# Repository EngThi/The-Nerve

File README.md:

# The Nerve Automation Motherboard

> [!IMPORTANT]
> Reviewer, this project is a custom board placed in Tier 3. To stay within the $100 budget including international shipping fees and taxes, Version A (Round TFT) is the primary build configuration. All components are hand-soldered.

The Nerve is a modular controller for automation workflows and video pipelines. It uses an ESP32-S3 for native Wi-Fi, Bluetooth, and USB HID support.

[Specs](#hardware) | [Logs](JOURNAL.md) | [Budget](BLUEPRINT_BUDGET.md) | [Production](hardware/production/)

---

## Hardware Design

The PCB was designed in EasyEDA and the enclosure in OnShape.

### Enclosure Design

- [OnShape Public Link](https://cad.onshape.com/documents/f5fe8f1a3f0d54ab7cd3f1d7/w/a16133ebbda184e0e50a9073/e/bf72140826f3054b8f947155?renderMode=0&uiState=6a2071693fc56d9f8f5e1dc7)
- [Tinkercad 3D Model](https://www.tinkercad.com/things/edG28wTrG8o-enclousure-the-nerve?sharecode=HdeJpYusIbuaaVPp3prye_n_lixCraDDIvdvkDYTo2M)

### PCB Layout

- [Project Link in the Editor](https://pro.easyeda.com/editor#id=794fe6f5b1b64e09b8597b022e057335)

### BOM (Version A - Round TFT)
| Part | Description | Price | Link |
| :--- | :--- | :--- | :--- |
| **ESP32-S3-DevKit-LiPo** | Native USB HID and built-in LiPo charging. | $8.70 | [Olimex](https://www.olimex.com/Products/IoT/ESP32-S3/ESP32-S3-DevKit-Lipo.html) |
| **Custom PCB (5pcs)** | 2-layer PCB fabrication. | $4.00 | JLCPCB |
| **Toggle Switch Missile Cover** | Safety arming switch | $3.73 | [AliExpress](https://aliexpress.com/item/1005006733525021.html) |
| **Outemu MX Switches (5pcs)** | Mechanical switches | $2.12 | [Shopee](https://shopee.com.br/Switch-Outemu-Para-Teclado-Mec%C3%A2nico-Diversas-Cores-Blue-Red-Brown-Green-Purple-Frete-Gr%C3%A1tis-i.374734112.23418702594?xptdk=89085a82-ef5b-4cdc-b985-b933109bc5e0) |
| **K-Silver JH16 Hall Joystick (2x)**| Hall Effect analog stick | $8.12 | [AliExpress](https://aliexpress.com/item/1005008728261473.html) |
| **EC11 Rotary Encoder (10pcs)** | Rotary input | $2.58 | [AliExpress](https://aliexpress.com/item/2001241262.html) |
| **JST-PH 2.0mm 2P Connector** | Required for battery connection | $1.31 | [AliExpress](https://aliexpress.com/item/33024777806.html) |
| **Round TFT GC9A01 Display** | 1.28 inch SPI display. | $1.38 | [AliExpress](https://aliexpress.com/item/1005008284550510.html) |
| **LiPo 1800mAh 3.7V Battery** | Standalone power source. | $5.05 | [Shopee](https://shopee.com.br/Bateria-Lipo-1800mah-3.7v-3-Fios-10x34x50-3-7v-Lithium-1s1p-i.389386479.55550251664?xptdk=ee7023c0-3a92-42a8-9799-b4aa47fd9676) |
| **SMD Components Batch** | LCSC Caps, Resistors, ICs (LS7183N-S) | $14.38 | LCSC |

*(Full details and shipping/taxes breakdown in the [Hardware Budget](BLUEPRINT_BUDGET.md) and [BOM CSV](the_nerve_bom.csv))*

---

## How to Use

So, The Nerve works like a node or a kind of independent trigger that communicates with your computer (or server, those types of HID interfaces, etc) to run automated tasks. I like the part of triggering n8n/general webhooks or running FFmpeg video processing scripts, controlling something on your PC

### Hardware Setup and Firmware Flashing
1. **Wire the Panel:** Connect the Joystick to the `ADC1` pins (Pins 1 and 2), the Rotary Encoder to the Quadrature Decoder pins (Pins 15 and 16) and the Cherry MX Switch and the Missile Toggle to their respective JST ports, according to the [Wiring Diagram](assets/diagrams/EXTERNAL_WIRING_GUIDE.png) that is right below. This way you can swap ports but they have to be compatible with the type of signal and mechanics of that device you are going to use.

2. **Flash the Firmware:** Connect the ESP32 via USB-C. Install MicroPython on the board and upload the `firmware/main.py` file (or whatever you develop for your own type of use). You can improve or change this entirely, since I developed it to be multi-use and very customizable. Use different types of components, parts, etc

3. **Turn on:** You can turn it on through the USB-C cable or totally independently using the 1800mAh LiPo battery (the ProS3 and even the new one from Olimex has built-in charging) . Upon turning on, it plays a startup tone and the RGB LED turns blue.

### Operation
- **Safety Switch (Safety Lock):** Before running any command, you must lift the switch cover and turn it on. The system will be armed and an LED indicator will light up.
- **Intensity Selector (Rotary Encoder):** Turn the encoder to adjust the "Intensity Level" (0 to 100). The RGB LED changes from blue to red to visually represent the intensity level you are setting for your automation task.

- **Timeline Navigation (Joystick):** Move the joystick to adjust the X/Y parameters (useful for navigating the timeline or adjusting the visual positioning in your scripts).
- **Execute (Cherry MX Switch):** Press the mechanical switch to fire the command. If the missile switch is *armed*, it will flash white, play an execution tone and send a JSON payload via serial (or via Wi-Fi through webhooks) containing all the dial and joystick parameters. If it's *disarmed*, it will flash red and play an error warning tone.

 Open n8n and import the workflows found in the `automation/n8n/flows/` directory.

The `trigger_executor.json` file brings a script that waits for a webhook.

A local Python script on your PC (or directly on the ESP32 via Wi-Fi) listens to the JSON serial output from The Nerve and forwards it to your n8n webhook (or wherever it is, kinda), which then parses the "Hype Level" and Joystick parameters to run the logic of the `video_pipeline.json` file.

I think that's pretty much it :P

---

---

## Build and Budget

The total delivered cost for Version A is **$99.77**.

Detailed evidence can be found in the [Hardware Budget](BLUEPRINT_BUDGET.md).

### Evidence Gallery

---

_Designed by ChefThi for Hack Club Blueprint._

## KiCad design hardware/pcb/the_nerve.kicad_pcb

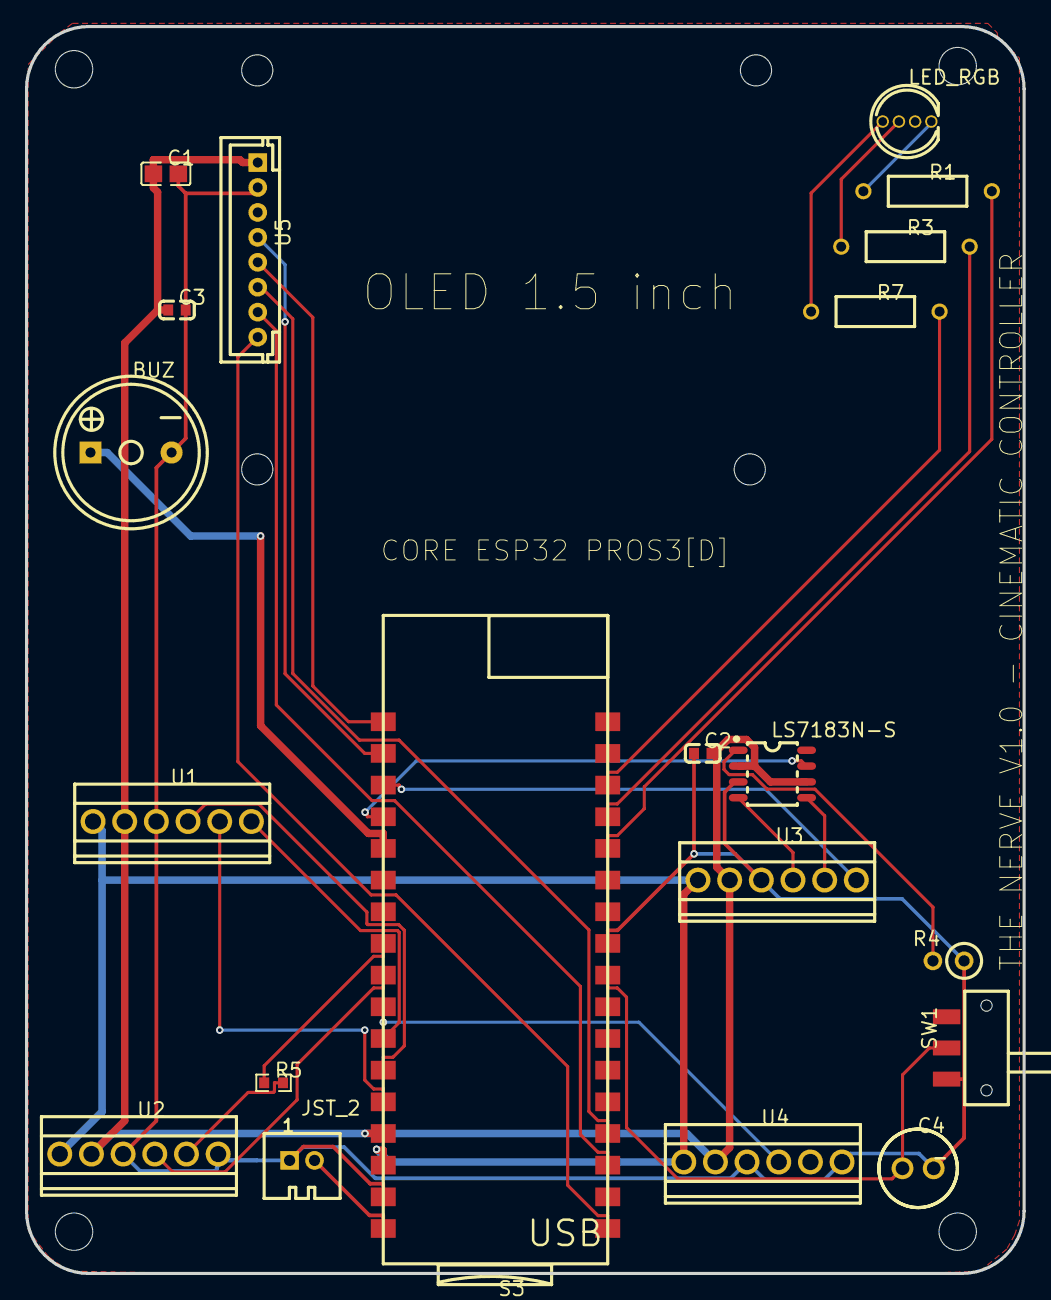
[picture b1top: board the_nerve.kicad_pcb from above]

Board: 2 copper layers, 80.0 x 100.0 mm, 20 parts (0 on the bottom side), 29 nets.

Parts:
BUZ: PASSIVE BUZZER
C1: C0805
C2, C3: 100nF; C0603
C4: 100uF; CAP-TH_BD6.3-P2.5-D0.6-FD-RYHG35V100UF
JST_2: 2.0-2P ZZDK; HDR-TH_2P-P2.00-V-F-2
LED_RGB: LED-RGB 共阴 插件 直径5MM; LED-TH_4P-BD5.8-P1.30
LS7183N-S: LS7183N-S; SOIC-8_L4.9-W3.9-P1.27-LS6.0-TL
R1, R3, R7: 220Ω; RES-TH_BD2.4-L6.3-P10.30-D0.6
R4: 2kΩ; RESISTOR-VERTICAL 1/4W 2.5MM
R5: R0603
S3: ESP32 ProS3; PROS3-SMD
SW1: MST-12D18G4 SPDT SLIDE SWITCH; SW-SMD_MST-12D18G4-SPDT-SLIDE-SWITCH
U1, U2, U3, U4: CONN-TH_6P-P2.54_KF128-2.54-6P
U5: CONN-TH_8P-P2.00_HCTL_PH-8A_C2908629

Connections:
3V3: C1.1, C2.2, C3.1, LS7183N-S.2, LS7183N-S.6, S3.4, U1.2, U2.2, U3.2, U4.2, U5.1
BUZZER: BUZ.1, S3.13
DOWN: LS7183N-S.7, S3.14
ENC_A: LS7183N-S.4, U3.4
ENC_B: LS7183N-S.5, U3.5
ENC_SW: S3.15, U3.6
GND_L: BUZ.2, C1.2, C2.1, C3.2, C4.2, JST_2.1, LS7183N-S.3, R4.1, S3.2, S3.25, SW1.1, U1.3, U2.3, U2.6, U3.3, U4.3, U4.6, U5.2
IO4: S3.8, U4.4
IO5: S3.9, U2.4
IO21: R5.2, U2.5
JOY_SW: S3.7, U1.6
JOY_X: S3.5, U1.5
JOY_Y: S3.6, U1.4
LED_BLUE: R7.2, S3.20
LED_GREEN: R3.2, S3.21
LED_RED: R1.2, S3.22
LED_RGB_1: LED_RGB.1, R1.1
LED_RGB_3: LED_RGB.3, R3.1
LED_RGB_4: LED_RGB.4, R7.1
LS7183N-S_1: LS7183N-S.1, R4.2
OLED_CS: S3.31, U5.6
OLED_DC: S3.32, U5.7
OLED_MOSI: S3.16, U5.4
OLED_RES: S3.34, U5.8
OLED_SCK: S3.17, U5.5
RST: C4.1, S3.26, SW1.2
S3_5V: S3.3, U1.1, U2.1, U3.1, U4.1
S3_10: R5.1, S3.10
VBAT: JST_2.2, S3.1

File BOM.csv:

ID,Name,Designator,Quantity,Manufacturer,Supplier,Supplier Part,Price,Link,Notes
1,C0805 10uF,C1,1,Samsung,LCSC,C96445,Decoupling Cap
2,Resistor 220Ω,R1/R3/R7,3,Tyohm,LCSC,C410657,0.01,https://jlcpcb.com/partdetail/TyoHM-RN_1_4W_220R_F_T_BA1/C410657,Current Limiting
3,Resistor 330Ω,R5,1,YAGEO,LCSC,C105881,0.0084,https://lcsc.com/product-detail/Chip-Resistor-Surface-Mount_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,LED Resistor
4,Resistor 2kΩ,R4,1,UNI-ROYAL,LCSC,C58680,0.008,https://www.lcsc.com/product-detail/C58680.html,Pull-up
5,Conn 6-Pin 2.54mm,U1-U4,4,KEFA,LCSC,C474924,0.637,https://lcsc.com/product-detail/Pluggable-System-Terminal-Bl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,Screw Terminals
6,Conn JST 2-Pin,JST_2,1,SHOU HAN,LCSC,C18185603,0.014,https://lcsc.com/product-detail/Wire-To-Board-Wire-To-Wire-C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,Battery Conn (2.0mm pitch)
7,Conn 8-Pin 2.00mm,U4_Ext,1,HCTL,LCSC,C2908629,0.044,https://lcsc.com/product-detail/Wire-To-Board-Wire-To-Wire-C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,Expansion Header
8,Passive Buzzer,BUZ,1,Generic,LCSC,C9900008742,0.0002,Audio Feedback
9,Cap 100nF,C2/C3,2,AIDE,LCSC,C49326605,0.0017,https://lcsc.com/product-detail/Multilayer-Ceramic-Capacitor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,Filter Cap
10,Cap 100uF,C4,1,HONOR,LCSC,C48970442,0.012,https://lcsc.com/product-detail/Aluminum-Electrolytic-Capaci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,Bulk Cap
11,LED RGB 5mm,LED_RGB,1,Generic,LCSC,C9900015469,0.0057,https://lcsc.com/product-detail/Light-Emitting-Diodes-LED_C9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,Status LED
12,IC Decoder LS7183N-S,U_DEC,1,LSI/CSI,LCSC,C3234982,6.32,https://lcsc.com/product-detail/Encoders_LSI-CSI-LS7183N-S_C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,Quadrature Decoder
13,Slide Switch SPDT,SW1,1,SHOU HAN,LCSC,C49023767,0.08,https://lcsc.com/product-detail/Slide-Switches_SHOU-HAN-MST-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,Power Switch
14,Battery LiPo 3000mAh,BATT_OPT1,1,Hiteuoms,Amazon,B0DP2JKFJG,9.99,https://www.amazon.com/dp/B0DP2JKFJG,"Power Source (Option 1, 3000mAh, JST 1.25mm - REQUIRES ADAPTER)"
15,Battery LiPo 2200mAh,BATT_OPT2,1,OXWINOU,Amazon,B0CTQ6VBB6,9.98,https://www.amazon.com/dp/B0CTQ6VBB6,"Power Source (Option 2, 2200mAh, JST 2.0mm - Direct Fit)"
16,Switch Cherry MX Blue,SW_MECH,1,Cherry,MechKeyboards,MX2A-Blue,0.50,https://mechanicalkeyboards.com/products/cherry-mx2a-blue-60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,Main Triggers (Clicky)
17,Toggle Switch Blue LED,SW_MISSILE,1,Adafruit,Adafruit,3306,3.95,https://www.adafruit.com/product/3306?srsltid=AfmBOorWMurQLX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,Safety Arming Switch
18,Joystick Hall Effect,JOY1,1,VGBUS,Amazon BR,B0CXDTGXZP,16.46,https://www.amazon.com.br/VGBUS-Qualitied-Effect-Joystick-Re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,Analog Control (Drift Free)
19,ESP32-S3 ProS3,U_MCU,1,Unexpected Maker,Adafruit,6398,26.50,https://www.adafruit.com/product/6398,Main Controller
20,OLED 1.5 RGB,DISP1,1,Waveshare,Waveshare,1.5inch RGB OLED,23.99,https://www.waveshare.com/1.5inch-rgb-oled-module.htm,Visual Interface

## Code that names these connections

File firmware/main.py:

import machine
import time
import json
from machine import Pin, ADC, PWM

# --- CONFIGURAÇÃO DE PINAGEM (MAPA OFICIAL PROS3) ---

# 1. Joystick (ADC1 - WiFi Safe)
# No ESP32-S3, os ADC1 são os pinos 1 a 10. O range é 12-bits (0 a 4095).
joy_x = ADC(Pin(1))
joy_y = ADC(Pin(2))
joy_sw = Pin(3, Pin.IN, Pin.PULL_UP)

# Atenuação de 11DB permite ler até ~3.1V (Perfeito para Joystick de 3.3V)
joy_x.atten(ADC.ATTN_11DB)
joy_y.atten(ADC.ATTN_11DB)

# 2. Encoder Óptico via LS7183N-S (Pulsos de Hardware)
# O chip LS7 entrega pulsos de UP e DOWN limpos. Não precisamos de debounce de hardware aqui.
enc_up = Pin(15, Pin.IN, Pin.PULL_UP)
enc_dn = Pin(16, Pin.IN, Pin.PULL_UP)
enc_sw = Pin(14, Pin.IN, Pin.PULL_UP)

# 3. Gatilhos Modulares JST
mx_switch = Pin(4, Pin.IN, Pin.PULL_UP)     # Execute (Cherry MX)
missile_sw = Pin(5, Pin.IN, Pin.PULL_UP)    # Safety Toggle
missile_led = Pin(21, Pin.OUT)              # LED da capa do switch

# 4. Feedbacks On-Board (PWM)
# No MicroPython do ESP32, o duty_u16 vai de 0 a 65535 (16 bits)
buzzer = PWM(Pin(18), freq=1000, duty_u16=0)
led_r = PWM(Pin(38), freq=5000, duty_u16=0)
led_g = PWM(Pin(39), freq=5000, duty_u16=0)
led_b = PWM(Pin(40), freq=5000, duty_u16=0)

# --- ESTADO DO SISTEMA ---
hype_level = 50
system_armed = False

def set_led(r, g, b):
    """
    Define a cor do LED RGB.
    Recebe (r,g,b) de 0 a 255 e converte para duty_u16 (0-65535).
    Se o seu LED for Cátodo Comum, maior valor = mais luz.
    Se for Ânodo Comum (como na maioria das devboards), inverta a lógica.
    """
    # Ex: r=255 -> 255 * 257 = 65535
    led_r.duty_u16(int(r * 257))
    led_g.duty_u16(int(g * 257)) 
    led_b.duty_u16(int(b * 257))

def play_alert(freq, duration):
    """Toca um tom no buzzer usando duty_u16 (50% = 32768)"""
    buzzer.freq(freq)
    buzzer.duty_u16(32768) # 50% de duty cycle (volume máximo)
    time.sleep(duration)
    buzzer.duty_u16(0)     # Desliga

# --- LÓGICA DO ENCODER LS7183N (PULSOS) ---
last_up = enc_up.value()
last_dn = enc_dn.value()

print("🎬 THE NERVE V1.0 - PROS3 EDITION ONLINE")
play_alert(2000, 0.2)
set_led(0, 50, 200) # Inicia Azul Cyperpack

while True:
    # 1. Gerenciamento de Segurança (Missile Switch)
    # Supondo que ligado (capa pra cima) feche para GND (0)
    system_armed = not missile_sw.value()
    missile_led.value(1 if system_armed else 0) # Acende LED do Missile se armado

    # 2. Hype Dial (Lógica para o chip LS7183N)
    curr_up = enc_up.value()
    curr_dn = enc_dn.value()
    
    # Detecta a borda de descida (quando o pino vai de 1 para 0)
    if curr_up == 0 and last_up == 1: 
        hype_level = min(100, hype_level + 5)
        # Gradient: 0 = Azul (0,0,255), 100 = Vermelho (255,0,0)
        set_led(int((hype_level/100)*255), 0, int(((100-hype_level)/100)*255)) 
    elif curr_dn == 0 and last_dn == 1: 
        hype_level = max(0, hype_level - 5)
        set_led(int((hype_level/100)*255), 0, int(((100-hype_level)/100)*255))
        
    last_up, last_dn = curr_up, curr_dn

    # 3. Timeline Scrubbing (Joystick)
    # ESP32-S3 ADC retorna 0 a 4095 (12 bits). Centro é ~2048.
    # Lemos read_u16 para ter mais precisão (0-65535) mas read() simples basta.
    # Normalizando ADC (0-4095) para Range de -100 a +100
    try:
        raw_x = joy_x.read()
        raw_y = joy_y.read()
        x_val = int((raw_x - 2048) / 20.48)
        y_val = int((raw_y - 2048) / 20.48)
        
        # Deadzone (ignora movimentos pequenos do dedo)
        if abs(x_val) < 10: x_val = 0
        if abs(y_val) < 10: y_val = 0
    except Exception as e:
        x_val, y_val = 0, 0

    # 4. Gatilho Final (Absolute Cinema Execution - Cherry MX)
    if not mx_switch.value():
        if system_armed:
            msg = {
                "event": "RENDER_NOW",
                "params": {
                    "hype": hype_level,
                    "scrub_x": x_val,
                    "scrub_y": y_val
                },
                "meta": "SHIP_IT"
            }
            print(json.dumps(msg)) # Envia para o n8n via Serial
            set_led(255, 255, 255) # Flash Branco (Cinema effect)
            play_alert(1500, 0.3)
            time.sleep(1) # Impede duplo clique acidental
        else:
            # Alerta de Segurança: Tentativa sem armar
            print(json.dumps({"warning": "SAFETY_LOCK_ACTIVE"}))
            set_led(255, 0, 0)
            play_alert(400, 0.1)
            time.sleep(0.5)

    time.sleep(0.01) # Loop a 100Hz para capturar o encoder rápido

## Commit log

2026-02-14 Organizaçao de tudo no repo além de terminar o README que já vinha pensando
2026-02-15 Deletei o case_v1.step
2026-02-19 feat(project): Documentação, BOM e Organização Geral do Projeto
    Atualiza e finaliza a Lista de Materiais (BOM), movendo-a para a raiz do projeto como 'BOM.csv'.
    A BOM agora inclui todos os componentes, com preços e links corrigidos, e apresenta duas opções de bateria com notas explicativas sobre a compatibilidade dos conectores.
    Melhora a documentação principal (README.md) com a adição de imagens do projeto, incluindo o render da PCB, o logo e uma prévia da fabricação.
    Reorganiza a estrutura de arquivos para alinhar com as melhores práticas.
    CORREÇÃO: Adiciona o README.md que foi modificado, mas esquecido no commit anterior.
2026-02-19 Just translated the README
2026-02-19 Clean up README and "```"
    Removed introductory text and Markdown code block from README.
2026-02-19 Add detailed development journal for Blueprint submission
2026-02-19 Delete assets/simulations directory
    Because I'll not use this more (I think)
2026-02-19 Align Journal dates with Blueprint timeline and add disclaimer
2026-02-20 Add schematic diagram to README
2026-02-20 feat(bom): Adiciona opções de encoders mecânico e óptico
    Adiciona o encoder mecânico Alps (EC11E15244B2) e o encoder óptico de alta precisão Bourns (ENA1J-B28-L00064L) à Lista de Materiais.
    Corrige a formatação geral do CSV e padroniza links de fornecedores para melhor legibilidade.
2026-02-20 docs: Atualiza custos totais e corrige quantidades na BOM
    Refaz o cálculo total de custo considerando todos os itens e opções da BOM (60.70).
    Corrige a quantidade do switch Cherry MX Blue para 1 unidade.
    Garante que a documentação reflita a estrutura completa de custos.
2026-02-20 Ajustes no firmware e arquivos do sistema
    - Adiciona mudanças no firmware.py esquecidas anteriormente.
    - Pequena correção no arquivo de configuração do IDX.
2026-02-21 Adiciona modelos 3D da case
    - Inclui os arquivos STL para o corpo principal, tampa e montagem completa.
    - Organiza os modelos na pasta hardware/3d_models/ com nomes padronizados.
2026-02-22 Adiciona renders da case do projeto
    - Inclui imagens da visão inferior, da case principal e juntas da case.
    - Organiza as imagens na pasta de assets com nomes descritivos.
2026-02-22 docs: Update JOURNAL with final slim premium case CAD details
2026-02-22 docs: Add mechanical hardware (wires, screws, inserts) to BOM
2026-02-22 docs: Update wire kit to specific BNTECHGO 10-color set and remove unnecessary mechanical items
2026-02-22 docs: Update JOURNAL replacing OpenSCAD with OnShape and add full CAD specifications
2026-02-22 docs: Update project total cost and add silicone wiring kit to BOM table
2026-02-22 docs: Update BOM with actual LCSC buzzer and RGB LED pack quantities and prices
2026-02-22 docs: Update README with new buzzer and RGB LED pack costs, total to $171.92
2026-02-23 Initial plan
2026-02-23 Replace BOM.csv with EasyEDA-generated 16-column JLCPCB/LCSC file
2026-02-23 docs: Update 10uF Capacitor to correct LCSC part C1713 with Cut Tape min qty 20
2026-02-23 docs: Add secondary BOM exclusively for JLCPCB assembly (PCBA) with correct 16-column format and updated C1713 capacitor
2026-02-23 Update hardware design files to v2026-02-23
    - Updates Gerbers, Pick and Place, and Schematic PDF to the latest versions.
    - Updates the PCB project JSON and adds the new OBJ 3D model.
    - Maintains the custom BOM.csv with updated prices and external modules.
2026-02-23 Fix URLs for encoders in BOM.csv
    Updated URLs for Mechanical and Optical Encoders in BOM.
2026-02-23 Correct quotes in BOM.csv
2026-02-23 Update JOURNAL.md with development progress and changes
    Documented the development progress, engineering decisions, and challenges faced during the development of The Nerve V1. Included updates on hardware changes, enclosure design, and BOM corrections.
2026-02-24 docs: Translate entire Journal to English, integrate Blueprint devlogs, and add final submission entry
2026-02-24 docs: Add journal images from assets/journal and include final PCB render
2026-02-25 Rename assets/renders/Untitled design (4).png to Board.png
2026-02-25 docs: Add banner disclaimer and hero image to README
2026-03-10 Fix formatting and remove extra newlines in README
    Removed unnecessary newline characters and fixed formatting in the README.
2026-03-10 fix: corrigir \n literais no README e melhorar formatação da Hardware Stack
2026-03-10 feat: add firmware/src/main.py and flashing guide (resolves empty src/ complaint)
2026-03-10 feat: add complete wiring diagram (hardware/schematics/WIRING_DIAGRAM.md)
2026-03-10 feat: add hardware/pcb/the_nerve.kicad_pro (resolves missing KiCad project file)
2026-03-10 Docs: Address review feedback
    - Removes legacy Rust firmware; MicroPython is now the standard.
    - Updates README to clarify firmware and CAD file status.
2026-03-11 docs: update cost table with real checkout prices by vendor (incl. shipping, PCBA, MOQ)
2026-03-11 Feat: Add new PCB design files from EasyEDA
    - Replaces the old KiCad project with the new EasyEDA project source (.json).
    - Adds the corresponding Gerber, BOM, and Pick & Place fabrication files for the new board revision.
    - Updates the README.md to reflect the change in design software (from KiCad to EasyEDA) and the new file structure.
2026-03-12 Fix: Replace hardware files with the correct version
    - Replaces all PCB and fabrication files with the correct, newly uploaded versions from EasyEDA.
    - Adds the STEP model of the PCB to the '3d_models' directory.
2026-03-12 docs: Finalize Hack Club Blueprint budget and sanitize repository structure
    - Generated official BLUEPRINT_BUDGET.md with validated, veracious checkout amounts.
    - Updated main BOMs to accurately reflect Minimum Order Quantities (MOQ) and shipping/handling fees.
    - Separated BOMs into LCSC and External sub-lists in hardware/fabrication/ to streamline parts sourcing.
    - Cleaned up root directory: Moved proof-of-purchase screenshots to assets/journal and renders to assets/renders.
    - Deleted redundant, unformatted EasyEDA export dumps.
    - Added 'Minimum Cost to Replicate' section to the main README.
2026-03-12 docs: clarify mandatory components and modular architecture for Hack Club review
    - Removed 'Optional' tags from batteries and encoders; both are mandatory for prototyping weight distribution and tactile feedback.
    - Explicitly documented the Motherboard/hand-wired approach in the README and Budget to explain why external parts are in the cart but not surface-mounted on the PCB render.
2026-03-12 docs: finalize assertive budget and modular design clarification for reviewer
    - Removed all 'optional' terminology from the project.
    - Updated BLUEPRINT_BUDGET.md to 17.84 (including MOQs and mandatory parts).
    - Clarified 'Motherboard Architecture' in README to explain external component mounting.
    - Verified enclosure design references in JOURNAL.md.
2026-03-12 docs: finalize wiring diagram terminology sync
2026-03-12 docs: finalize verified budget at 87.47 based on latest checkout screenshots
2026-03-13 docs: complete README with firmware setup, 3D source info, and verified budget
2026-03-15 docs: add eye-catching reviewer note to top of README
2026-03-17 docs: organize images and add case renders to README for reviewer clarity
2026-03-19 docs: update budget and add AliExpress cart to reduce project costs
2026-03-19 docs: move and update official BOM to root with AliExpress links
2026-03-19 docs: simplify BOM and move regional tax/freight notes to README
2026-03-19 docs: update journal logs
2026-03-19 docs: final technical revision of README
2026-03-21 docs: comprehensive project overhaul for resubmission (budget optimization, technical journal, and direct README)
2026-03-22 Add link to OnShape 3D model
2026-03-22 docs: final refinement to address minor reviewer feedback on manufacturing files and automation flows
2026-03-22 docs: expand journal with detailed engineering logs and final optimization
2026-03-24 docs: finalize Tier 3 optimization with cheaper encoder, wiring diagram, and standalone justification
2026-03-24 docs: overhaul journals to raw engineering log format
2026-03-25 docs: finalize tier 3 budget and sync BOM with new shopping cart evidence
2026-03-26 docs: finalized engineering logs with image references and technical details
2026-03-26 docs: rewrite journal in authentic voice, align with real commit history
2026-03-27 docs: add time spent per session to journal entries
2026-03-27 docs: adjust build log hours to reflect ~85h total development time
2026-03-30 docs: restructure journal into granular step-by-step entries per reviewer feedback
2026-03-30 docs: upgrade repository to professional standards (production folder and technical spec layout)
2026-03-31 docs: rewrite README in plain developer voice, remove AI-looking patterns
2026-03-31 refactor: rewrite journal as authentic engineering log, add inline images
2026-03-31 docs: final resubmission overhaul with visual wiring guide and gold standard README
2026-04-05 Update budget tier from Tier 3 to Tier 2
2026-04-13 docs: resolve conflicts and apply final technical polish for resubmission
2026-04-13 docs: strictly optimize budget to ~8 by removing PCBA and using manual SMT assembly
2026-04-13 docs: restore reviewer note and embed wiring guide image
2026-04-15 docs: rewrite the README and JOURNAL for reviewer
2026-04-15 docs: rewrite the README and JOURNAL for reviewer :(
2026-04-18 Update README with schematic and battery info
    Added schematic section and updated battery description.
2026-04-22 Update budget with final component prices and add receipt screenshots
2026-05-06 docs: final budget alignment and May 5th update
2026-05-06 docs: restore colorful enclosure renders as hero images
2026-05-06 Remove Enclosure Top View image from README
    Removed the Enclosure Top View image from the README.
2026-05-07 Revise final estimated hardware cost in JOURNAL.md
    Updated final estimated hardware cost to $89.79 and ensured documentation accuracy for grant submission.
2026-05-07 Correct hardware cost in README
    Updated hardware cost from $89.55 to $89.79.
2026-05-07 Revise
2026-05-07 docs: revise journal and final budget
2026-05-07 formated important
2026-06-06 docs: finalize the nerve version C and sync edge-nexus submodule
2026-06-06 docs: remove unintended edge-nexus folder
2026-06-06 docs: sync latest manufacturing files and update OnShape link
2026-06-06 docs: update AliExpress links and connector price
2026-06-06 docs: adjust budget and designate Version A for Tier 3 compliance
2026-06-06 docs: organize final budget proofs and update documentation to Version A
2026-06-06 docs: finalize README and Budget with Version A and cart links
2026-06-06 docs: add EasyEDA project link to hardware design section
2026-06-06 docs: Refactor budget to separate base parts from shipping, add usage instructions, add Tinkercad link, and update fabrication files
2026-06-06 docs: Add prices and links to the BOM table in README
2026-06-06 docs: Fix Shopee links and Outemu switch quantity in BOM
2026-06-06 fix: Resolve illegal CSV quoting on lines 13 and 14
2026-06-06 fix: Remove comment lines to fix CSV column structure
2026-06-06 fix: Wrap notes column in quotes on line 12 to prevent extra CSV columns
2026-06-06 docs: Finalize unified master BOM with all external components, links, and technical specs
2026-06-07 fix: csv commas

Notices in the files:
README.md:
Hardware License
